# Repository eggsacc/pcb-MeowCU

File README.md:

<div align="center">

# MeowCU

4-layer **STM32F405RGT6 MeowCU** 🐱 (MCU) dev module with commonly used peripherals broken out for easy access, and a dedicated CAN transceiver. Also includes 2 user programmable buttons and mini OLED display.

>3D render - Front

>Back

## Layout (all layers)

</div>

## MCU Pinout

<div align="center">

| Breakout / feature | Peripheral | Pin mapping |
|---|---|---|
| **UART header** | `USART3` | TX &rarr; `PC10`<br>RX &rarr; `PC11` |
| **SPI header** | `SPI1` | CS &rarr; `PA4`<br>SCK &rarr; `PA5`<br>MISO &rarr; `PA6`<br>MOSI &rarr; `PA7` |
| **I2C header** | `I2C1` | SCL &rarr; `PB6`<br>SDA &rarr; `PB7` |
| **CAN screw terminal** | `CAN1` (SN65HVD230) | TX &rarr; `PB9`<br>RX &rarr; `PB8` |
| **USB-C** | `USB_OTG_FS` | D&minus; &rarr; `PA11`<br>D+ &rarr; `PA12` |
| **SWD header** | `SYS` | SWDIO &rarr; `PA13`<br>SWCLK &rarr; `PA14` |
| **3-phase PWM header** | `TIM1` | <table><tbody><tr><td align="right">CH1 &rarr;</td><td><code>PA8</code></td><td align="right">&emsp;C1N &rarr;</td><td><code>PB13</code></td></tr><tr><td align="right">CH2 &rarr;</td><td><code>PA9</code></td><td align="right">&emsp;C2N &rarr;</td><td><code>PB0</code></td></tr><tr><td align="right">CH3 &rarr;</td><td><code>PA10</code></td><td align="right">&emsp;C3N &rarr;</td><td><code>PB1</code></td></tr></tbody></table> |
| **OLED** (on-board) | `I2C2` | SCL &rarr; `PB10`<br>SDA &rarr; `PB11` |
| **Utility buttons** (on-board) | `GPIO` / `EXTI` | L button &rarr; `PA2`<br>R button &rarr; `PA3` |
| **Crystal** (25MHz) | `RCC` HSE | OSC_IN &rarr; `PH0`<br>OSC_OUT &rarr; `PH1` |
| **GPIO header** (2&times;10) | free GPIO | <table><tbody><tr><td align="right">1 &rarr;</td><td><code>3.3V</code></td><td align="right">&emsp;2 &rarr;</td><td><code>3.3V</code></td></tr><tr><td align="right">3 &rarr;</td><td><code>5V</code></td><td align="right">&emsp;4 &rarr;</td><td><code>5V</code></td></tr><tr><td align="right">5 &rarr;</td><td><code>GND</code></td><td align="right">&emsp;6 &rarr;</td><td><code>GND</code></td></tr><tr><td align="right">7 &rarr;</td><td><code>PB4</code></td><td align="right">&emsp;8 &rarr;</td><td><code>PB3</code></td></tr><tr><td align="right">9 &rarr;</td><td><code>PC12</code></td><td align="right">&emsp;10 &rarr;</td><td><code>PC2</code></td></tr><tr><td align="right">11 &rarr;</td><td><code>PC3</code></td><td align="right">&emsp;12 &rarr;</td><td><code>PA0</code></td></tr><tr><td align="right">13 &rarr;</td><td><code>PA1</code></td><td align="right">&emsp;14 &rarr;</td><td><code>PC9</code></td></tr><tr><td align="right">15 &rarr;</td><td><code>PC8</code></td><td align="right">&emsp;16 &rarr;</td><td><code>PC7</code></td></tr><tr><td align="right">17 &rarr;</td><td><code>PC6</code></td><td align="right">&emsp;18 &rarr;</td><td><code>PB15</code></td></tr><tr><td align="right">19 &rarr;</td><td><code>PB14</code></td><td align="right">&emsp;20 &rarr;</td><td><code>PB12</code></td></tr></tbody></table> |

**Buttons are active-low to GND (3V3 pull-up).*
</div>

## Power mux

The external 5V pin and USB `vbus` are separate rails; a power mux IC (TPS2116) automatically switches to the external 5V rail when connected.

---

<div align="center">
Designed by <b>@eggsacc</b> · MeowCU V1.6<br>
Updated 09/10/2026
</div>

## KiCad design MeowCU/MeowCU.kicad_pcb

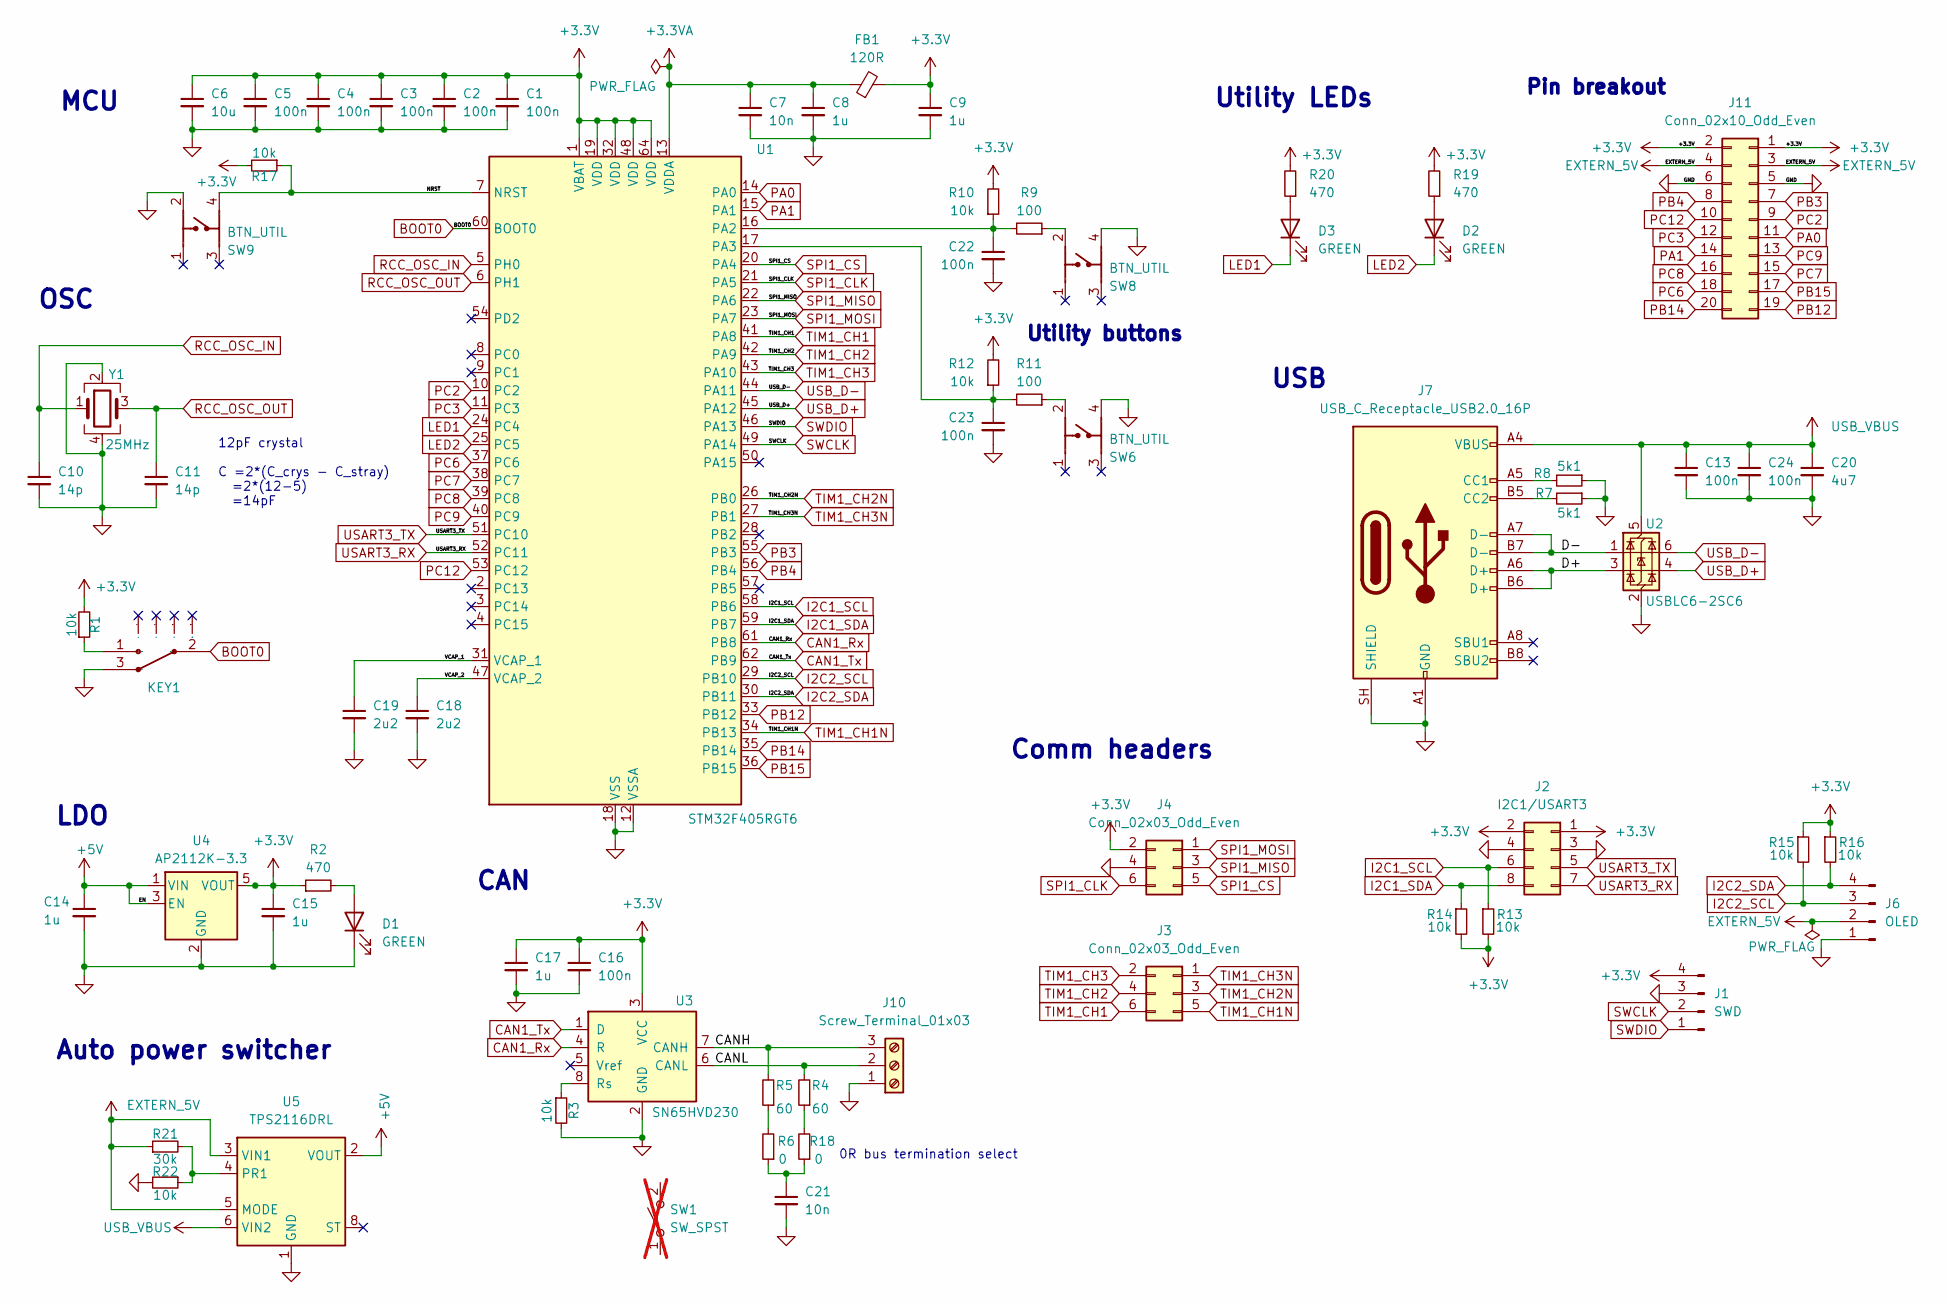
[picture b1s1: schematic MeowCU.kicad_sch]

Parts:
C1, C2, C3, C4, C5, C13, C16, C22, C23, C24: 100n; C_0402_1005Metric
C6: 10u; C_0603_1608Metric
C7, C21: 10n; C_0402_1005Metric
C8, C9, C17: 1u; C_0402_1005Metric
C10, C11: 14p; C_0402_1005Metric
C14, C15: 1u; C_0603_1608Metric
C18, C19: 2u2; C_0603_1608Metric
C20: 4u7; C_0603_1608Metric
D1, D2, D3: GREEN; LED_0402_1005Metric
FB1: 120R; L_0603_1608Metric
J1: SWD; JST_SH_SM04B-SRSS-TB_1x04-1MP_P1.00mm_Horizontal
J2: I2C1/USART3; PinSocket_2x04_P2.54mm_Vertical
J3, J4: Conn_02x03_Odd_Even; PinSocket_2x03_P2.54mm_Vertical
J6: OLED; OLED header
J7: USB_C_Receptacle_USB2.0_16P; USB_C_Receptacle_HRO_TYPE-C-31-M-12
J10: Screw_Terminal_01x03; TerminalBlock_Phoenix_MKDS-1-3-3.81_1x03_P3.81mm_Horizontal
J11: Conn_02x10_Odd_Even; PinSocket_2x10_P2.54mm_Vertical
KEY1: MSK-11027 Toggle Switches; SW-SMD_MSK-11027; Manufacturer Part MSK-11027 Toggle Switches
R1, R3, R10, R12, R13, R14, R15, R16, R17, R22: 10k; R_0402_1005Metric
R2, R19, R20: 470; R_0402_1005Metric
R4, R5: 60; R_0402_1005Metric
R6, R18: 0; R_1206_3216Metric_Pad1.30x1.75mm_HandSolder
R7, R8: 5k1; R_0402_1005Metric
R9, R11: 100; R_0402_1005Metric
R21: 30k; R_0402_1005Metric
SW1: SW_SPST; SW_DIP_SPSTx01_Slide_Copal_CHS-01A_W5.08mm_P1.27mm_JPin; not fitted
SW6, SW8, SW9: BTN_UTIL; SW-SMD_4P-L4.2-W3.4-P2.15-LS5.2; Manufacturer Part HX 3x4x2.5-PA-4N push button switch
U1: STM32F405RGT6; LQFP-64_10x10mm_P0.5mm
U2: USBLC6-2SC6; SOT-23-6
U3: SN65HVD230; SOIC-8_3.9x4.9mm_P1.27mm
U4: AP2112K-3.3; SOT-23-5_HandSoldering
U5: TPS2116DRL; SOT-583-8
Y1: 25MHz; Crystal_SMD_3225-4Pin_3.2x2.5mm

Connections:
+3.3V: C1.1, C2.1, C3.1, C4.1, C5.1, C6.1, C9.1, C15.1, C16.1, C17.1, FB1.2, J1.4, J2.1, J2.2, J4.2, J11.1, J11.2, R1.2, R2.1, R10.2, R12.2, R13.2, R14.2, R15.1, R16.1, R17.2, R19.2, R20.2, U1.1 (VBAT), U1.19 (VDD), U1.32 (VDD), U1.48 (VDD), U1.64 (VDD), U3.3 (VCC), U4.5 (VOUT)
+3.3VA: C7.1, C8.1, FB1.1, U1.13 (VDDA)
+5V: C14.1, U4.1 (VIN), U4.3 (EN), U5.2 (VOUT), U5.7 (VOUT)
/CANH: J10.3, R5.2, U3.7 (CANH)
/CANL: J10.2, R4.2, U3.6 (CANL)
/D+: J7.A6 (D+), J7.B6 (D+), U2.3 (I/O2)
/D-: J7.A7 (D-), J7.B7 (D-), U2.1 (I/O1)
/NRST: R17.1, SW9.4, U1.7 (NRST)
/VCAP_1: C19.1, U1.31 (VCAP_1)
/VCAP_2: C18.1, U1.47 (VCAP_2)
BOOT0: KEY1.2, U1.60 (BOOT0)
CAN1_Rx: U1.61 (PB8), U3.4 (R)
CAN1_Tx: U1.62 (PB9), U3.1 (D)
EXTERN_5V: J6.2, J11.3, J11.4, R21.1, U5.3 (VIN1), U5.5 (MODE)
GND: C1.2, C2.2, C3.2, C4.2, C5.2, C6.2, C7.2, C8.2, C9.2, C10.2, C11.2, C13.2, C14.2, C15.2, C16.2, C17.2, C18.2, C19.2, C20.2, C21.2, C22.2, C23.2, C24.2, D1.1 (K), J1.3, J2.3, J2.4, J4.4, J6.1, J7.A1 (GND), J7.A12 (GND), J7.B1 (GND), J7.B12 (GND), J7.SH (SHIELD), J10.1, J11.5, J11.6, KEY1.3, R3.2, R7.1, R8.1, R22.2, SW6.4, SW8.4, SW9.2, U1.12 (VSSA), U1.18 (VSS), U1.63 (VSS), U2.2 (GND), U3.2 (GND), U4.2 (GND), U5.1 (GND), Y1.2, Y1.4
I2C1_SCL: J2.6, R13.1, U1.58 (PB6)
I2C1_SDA: J2.8, R14.1, U1.59 (PB7)
I2C2_SCL: J6.3, R15.2, U1.29 (PB10)
I2C2_SDA: J6.4, R16.2, U1.30 (PB11)
LED1: D3.1 (K), U1.24 (PC4)
LED2: D2.1 (K), U1.25 (PC5)
unnamed: C21.1, R6.1, R18.1
unnamed: D1.2 (A), R2.2
unnamed: D2.2 (A), R19.1
unnamed: D3.2 (A), R20.1
unnamed: J7.A5 (CC1), R8.2
unnamed: J7.B5 (CC2), R7.2
unnamed: KEY1.1, R1.1
unnamed: R5.1, R6.2
unnamed: R9.1, SW8.2
unnamed: R11.1, SW6.2
unnamed: R4.1, R18.2
unnamed: C22.1, R9.2, R10.1, U1.16 (PA2)
unnamed: C23.1, R11.2, R12.1, U1.17 (PA3)
unnamed: R3.1, U3.8 (Rs)
unnamed: R21.2, R22.1, U5.4 (PR1)
PA0: J11.11, U1.14 (PA0)
PA1: J11.14, U1.15 (PA1)
PB3: J11.7, U1.55 (PB3)
PB4: J11.8, U1.56 (PB4)
PB12: J11.19, U1.33 (PB12)
PB14: J11.20, U1.35 (PB14)
PB15: J11.17, U1.36 (PB15)
PC2: J11.9, U1.10 (PC2)
PC3: J11.12, U1.11 (PC3)
PC6: J11.18, U1.37 (PC6)
PC7: J11.15, U1.38 (PC7)
PC8: J11.16, U1.39 (PC8)
PC9: J11.13, U1.40 (PC9)
PC12: J11.10, U1.53 (PC12)
RCC_OSC_IN: C10.1, U1.5 (PH0), Y1.1
RCC_OSC_OUT: C11.1, U1.6 (PH1), Y1.3
SPI1_CLK: J4.6, U1.21 (PA5)
SPI1_CS: J4.5, U1.20 (PA4)
SPI1_MISO: J4.3, U1.22 (PA6)
SPI1_MOSI: J4.1, U1.23 (PA7)
SWCLK: J1.2, U1.49 (PA14)
SWDIO: J1.1, U1.46 (PA13)
TIM1_CH1: J3.6, U1.41 (PA8)
TIM1_CH1N: J3.5, U1.34 (PB13)
TIM1_CH2: J3.4, U1.42 (PA9)
TIM1_CH2N: J3.3, U1.26 (PB0)
TIM1_CH3: J3.2, U1.43 (PA10)
TIM1_CH3N: J3.1, U1.27 (PB1)
USART3_RX: J2.7, U1.52 (PC11)
USART3_TX: J2.5, U1.51 (PC10)
USB_D+: U1.45 (PA12), U2.4 (I/O2)
USB_D-: U1.44 (PA11), U2.6 (I/O1)
USB_VBUS: C13.1, C20.1, C24.1, J7.A4 (VBUS), J7.A9 (VBUS), J7.B4 (VBUS), J7.B9 (VBUS), U2.5 (VBUS), U5.6 (VIN2)

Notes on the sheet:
Auto power switcher
MCU
Pin breakout
Comm headers
CAN
Utility LEDs
12pF crystal C =2*(C_crys - C_stray) =2*(12-5) =14pF
USB
Utility buttons
LDO
OSC
0R bus termination select

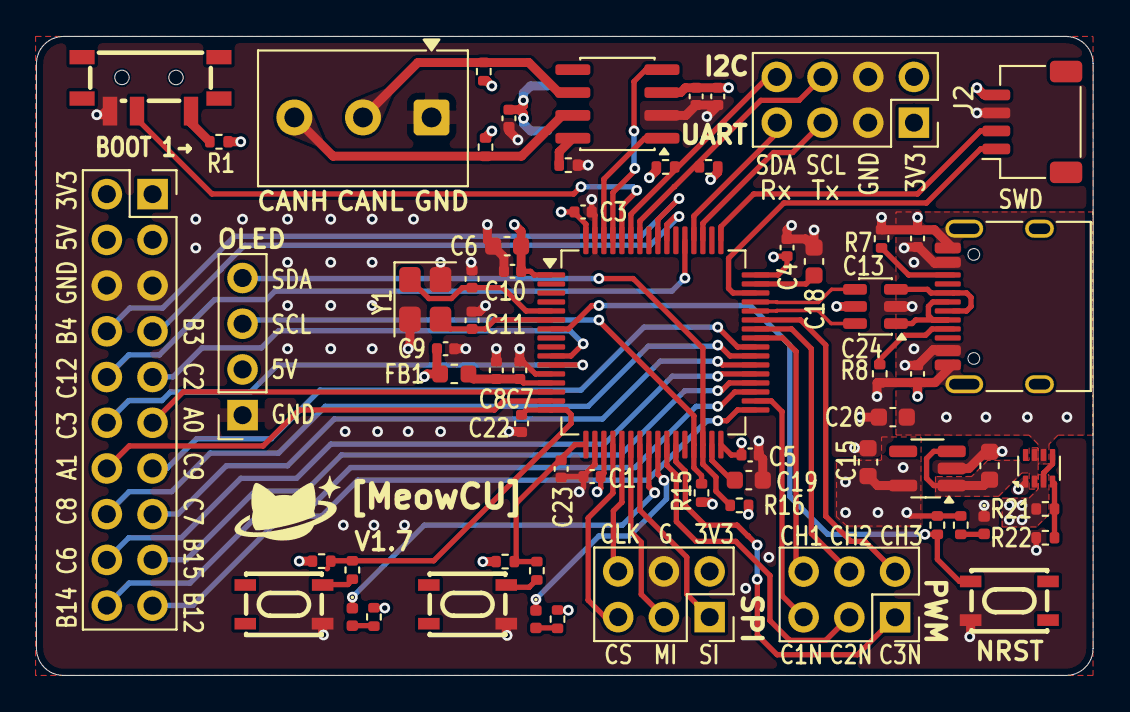
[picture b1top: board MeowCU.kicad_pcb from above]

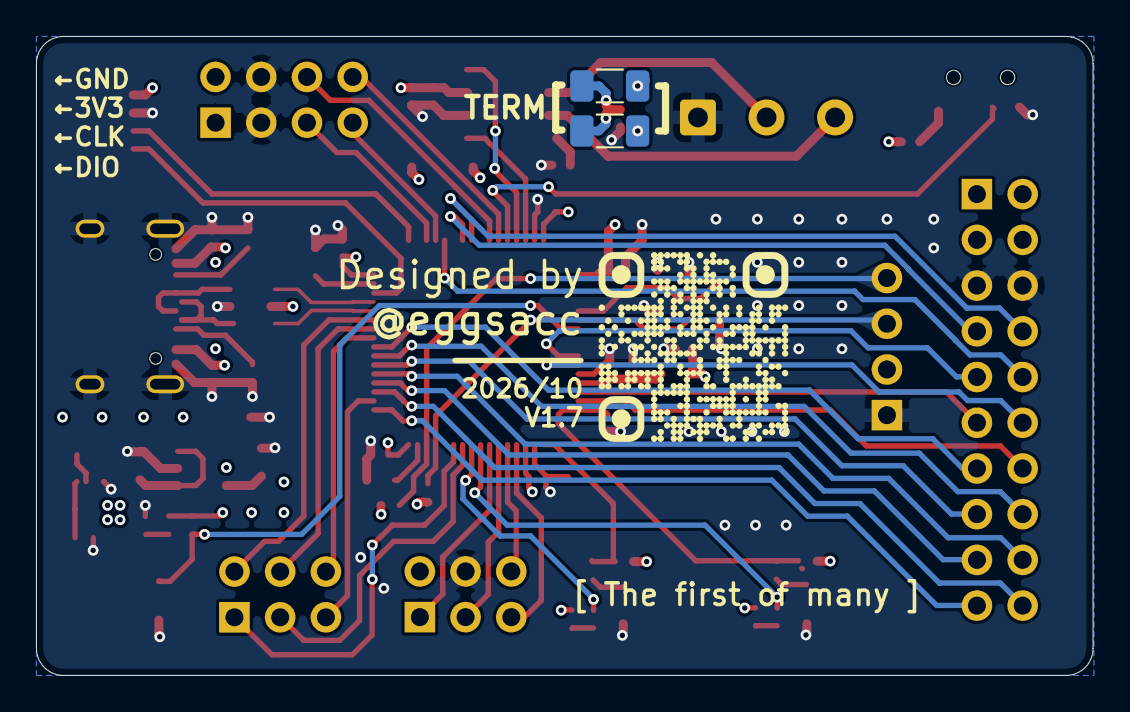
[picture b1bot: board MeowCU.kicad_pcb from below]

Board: 4 copper layers, 58.7 x 35.5 mm, 67 parts (2 on the bottom side), 69 nets.

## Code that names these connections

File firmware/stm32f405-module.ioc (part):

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Mcu.Name=STM32F405RGTx
Mcu.Package=LQFP64
Mcu.UserName=STM32F405RGTx
PA0-WKUP.GPIOParameters=GPIO_Label
PA0-WKUP.GPIO_Label=SOA
PA0-WKUP.Signal=ADCx_IN0
PA1.GPIOParameters=GPIO_Label
PA1.GPIO_Label=VIN_SENSE
PA1.Signal=ADCx_IN1
PA10.Signal=S_TIM1_CH3
PA11.Mode=Device_Only
PA11.Signal=USB_OTG_FS_DM
PA12.Mode=Device_Only
PA12.Signal=USB_OTG_FS_DP
PA13.Mode=Serial_Wire
PA13.Signal=SYS_JTMS-SWDIO
PA14.Mode=Serial_Wire
PA14.Signal=SYS_JTCK-SWCLK
PA2.GPIOParameters=GPIO_Label
PA2.GPIO_Label=GPIO_EXTI2(Push1)
PA2.Signal=GPXTI2
PA3.GPIOParameters=GPIO_Label
PA3.GPIO_Label=GPIO_EXTI3(Push2)
PA3.Signal=GPXTI3
PA4.GPIOParameters=GPIO_Label
PA4.GPIO_Label=SPI1_CS
PA4.Signal=GPIO_Output
PA5.Mode=Full_Duplex_Master
PA5.Signal=SPI1_SCK
PA6.Mode=Full_Duplex_Master
PA6.Signal=SPI1_MISO
PA7.Mode=Full_Duplex_Master
PA7.Signal=SPI1_MOSI
PA8.Signal=S_TIM1_CH1
PA9.Signal=S_TIM1_CH2
PB0.Mode=PWM Generation2 CH2 CH2N
PB0.Signal=TIM1_CH2N
PB1.Mode=PWM Generation3 CH3 CH3N
PB1.Signal=TIM1_CH3N
PB10.GPIOParameters=GPIO_Label
PB10.GPIO_Label=I2C2_SCL(OLED)
PB10.Mode=I2C
PB10.Signal=I2C2_SCL
PB11.GPIOParameters=GPIO_Label
PB11.GPIO_Label=I2C2_SDA(OLED)
PB11.Mode=I2C
PB11.Signal=I2C2_SDA
PB13.Mode=PWM Generation1 CH1 CH1N
PB13.Signal=TIM1_CH1N
PB3.GPIOParameters=GPIO_Label
PB3.GPIO_Label=nSCS
PB3.Signal=GPIO_Output
PB4.GPIOParameters=GPIO_Label
PB4.GPIO_Label=nFAULT
PB4.Signal=GPIO_Output
PB6.Mode=I2C
PB6.Signal=I2C1_SCL
PB7.Mode=I2C
PB7.Signal=I2C1_SDA
PB8.Mode=CAN_Activate
PB8.Signal=CAN1_RX
PB9.Mode=CAN_Activate
PB9.Signal=CAN1_TX
PC10.Mode=Asynchronous
PC10.Signal=USART3_TX
PC11.Mode=Asynchronous
PC11.Signal=USART3_RX
PC12.GPIOParameters=GPIO_Label
PC12.GPIO_Label=DRV8316_CS
PC12.Signal=GPIO_Output
PC2.GPIOParameters=GPIO_Label
PC2.GPIO_Label=SOC
PC2.Signal=ADCx_IN12
PC3.GPIOParameters=GPIO_Label
PC3.GPIO_Label=SOB
PC3.Signal=ADCx_IN13
PH0-OSC_IN.Mode=HSE-External-Oscillator
PH0-OSC_IN.Signal=RCC_OSC_IN
PH1-OSC_OUT.Mode=HSE-External-Oscillator
PH1-OSC_OUT.Signal=RCC_OSC_OUT
RCC.HSE_VALUE=25000000
RCC.SYSCLKFreq_VALUE=168000000
RCC.SYSCLKSource=RCC_SYSCLKSOURCE_PLLCLK
board=custom

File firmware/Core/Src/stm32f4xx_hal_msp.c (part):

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    __HAL_RCC_GPIOC_CLK_ENABLE();
    __HAL_RCC_GPIOA_CLK_ENABLE();
    /**ADC1 GPIO Configuration
    PC2     ------> ADC1_IN12
    PC3     ------> ADC1_IN13
    PA0-WKUP     ------> ADC1_IN0
    PA1     ------> ADC1_IN1
    */
    GPIO_InitStruct.Pin = SOC_Pin|SOB_Pin;
    GPIO_InitStruct.Mode = GPIO_MODE_ANALOG;
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    __HAL_RCC_ADC1_CLK_DISABLE();

    /**ADC1 GPIO Configuration
    PC2     ------> ADC1_IN12
    PC3     ------> ADC1_IN13
    PA0-WKUP     ------> ADC1_IN0
    PA1     ------> ADC1_IN1
    */
    HAL_GPIO_DeInit(GPIOC, SOC_Pin|SOB_Pin);

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
    __HAL_RCC_GPIOB_CLK_ENABLE();
    /**CAN1 GPIO Configuration
    PB8     ------> CAN1_RX
    PB9     ------> CAN1_TX
    */
    GPIO_InitStruct.Pin = GPIO_PIN_8|GPIO_PIN_9;
    GPIO_InitStruct.Mode = GPIO_MODE_AF_PP;
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    __HAL_RCC_CAN1_CLK_DISABLE();

    /**CAN1 GPIO Configuration
    PB8     ------> CAN1_RX
    PB9     ------> CAN1_TX
    */
    HAL_GPIO_DeInit(GPIOB, GPIO_PIN_8|GPIO_PIN_9);

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
    __HAL_RCC_GPIOB_CLK_ENABLE();
    /**I2C1 GPIO Configuration
    PB6     ------> I2C1_SCL
    PB7     ------> I2C1_SDA
    */
    GPIO_InitStruct.Pin = GPIO_PIN_6|GPIO_PIN_7;
    GPIO_InitStruct.Mode = GPIO_MODE_AF_OD;
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
    __HAL_RCC_GPIOB_CLK_ENABLE();
    /**I2C2 GPIO Configuration
    PB10     ------> I2C2_SCL
    PB11     ------> I2C2_SDA
    */
    GPIO_InitStruct.Pin = I2C2_SCL_Pin|I2C2_SDA_Pin;
    GPIO_InitStruct.Mode = GPIO_MODE_AF_OD;
    GPIO_InitStruct.Pull = GPIO_NOPULL;
    GPIO_InitStruct.Speed = GPIO_SPEED_FREQ_VERY_HIGH;
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    __HAL_RCC_I2C1_CLK_DISABLE();

    /**I2C1 GPIO Configuration
    PB6     ------> I2C1_SCL
    PB7     ------> I2C1_SDA
    */
    HAL_GPIO_DeInit(GPIOB, GPIO_PIN_6);

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    __HAL_RCC_I2C2_CLK_DISABLE();

    /**I2C2 GPIO Configuration
    PB10     ------> I2C2_SCL
    PB11     ------> I2C2_SDA
    */
    HAL_GPIO_DeInit(I2C2_SCL_GPIO_Port, I2C2_SCL_Pin);

    HAL_GPIO_DeInit(I2C2_SDA_GPIO_Port, I2C2_SDA_Pin);

    /* USER CODE BEGIN I2C2_MspDeInit 1 */

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
    __HAL_RCC_GPIOA_CLK_ENABLE();
    /**SPI1 GPIO Configuration
    PA5     ------> SPI1_SCK
    PA6     ------> SPI1_MISO
    PA7     ------> SPI1_MOSI
    */
    GPIO_InitStruct.Pin = GPIO_PIN_5|GPIO_PIN_6|GPIO_PIN_7;
    GPIO_InitStruct.Mode = GPIO_MODE_AF_PP;
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    __HAL_RCC_SPI1_CLK_DISABLE();

    /**SPI1 GPIO Configuration
    PA5     ------> SPI1_SCK
    PA6     ------> SPI1_MISO
    PA7     ------> SPI1_MOSI
    */
    HAL_GPIO_DeInit(GPIOA, GPIO_PIN_5|GPIO_PIN_6|GPIO_PIN_7);

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    __HAL_RCC_GPIOB_CLK_ENABLE();
    __HAL_RCC_GPIOA_CLK_ENABLE();
    /**TIM1 GPIO Configuration
    PB0     ------> TIM1_CH2N
    PB1     ------> TIM1_CH3N
    PB13     ------> TIM1_CH1N
    PA8     ------> TIM1_CH1
    PA9     ------> TIM1_CH2
    PA10     ------> TIM1_CH3
    */
    GPIO_InitStruct.Pin = GPIO_PIN_0|GPIO_PIN_1|GPIO_PIN_13;
    GPIO_InitStruct.Mode = GPIO_MODE_AF_PP;
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
    __HAL_RCC_GPIOC_CLK_ENABLE();
    /**USART3 GPIO Configuration
    PC10     ------> USART3_TX
    PC11     ------> USART3_RX
    */
    GPIO_InitStruct.Pin = GPIO_PIN_10|GPIO_PIN_11;
    GPIO_InitStruct.Mode = GPIO_MODE_AF_PP;
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    __HAL_RCC_USART3_CLK_DISABLE();

    /**USART3 GPIO Configuration
    PC10     ------> USART3_TX
    PC11     ------> USART3_RX
    */
    HAL_GPIO_DeInit(GPIOC, GPIO_PIN_10|GPIO_PIN_11);

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

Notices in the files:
firmware/Core/Src/stm32f4xx_hal_msp.c:
Copyright (c) 2026 STMicroelectronics.
All rights reserved.
This software is licensed under terms that can be found in the LICENSE file
